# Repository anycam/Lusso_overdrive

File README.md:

# Lusso Overdrive
###### Get a crunch and boost !

This guitar pedal is based on the Klon centaur and the well knwon green friend TS, adding a 2 band EQ for low pass and high pass filtering along with a two modes bypass using two relays and an PIC uC programmed in C++.

Feel free to make your own pedal, here you can find the schematic, pcb and gerber files ready to send into your favorite pcb manufacturer.

## Gallery

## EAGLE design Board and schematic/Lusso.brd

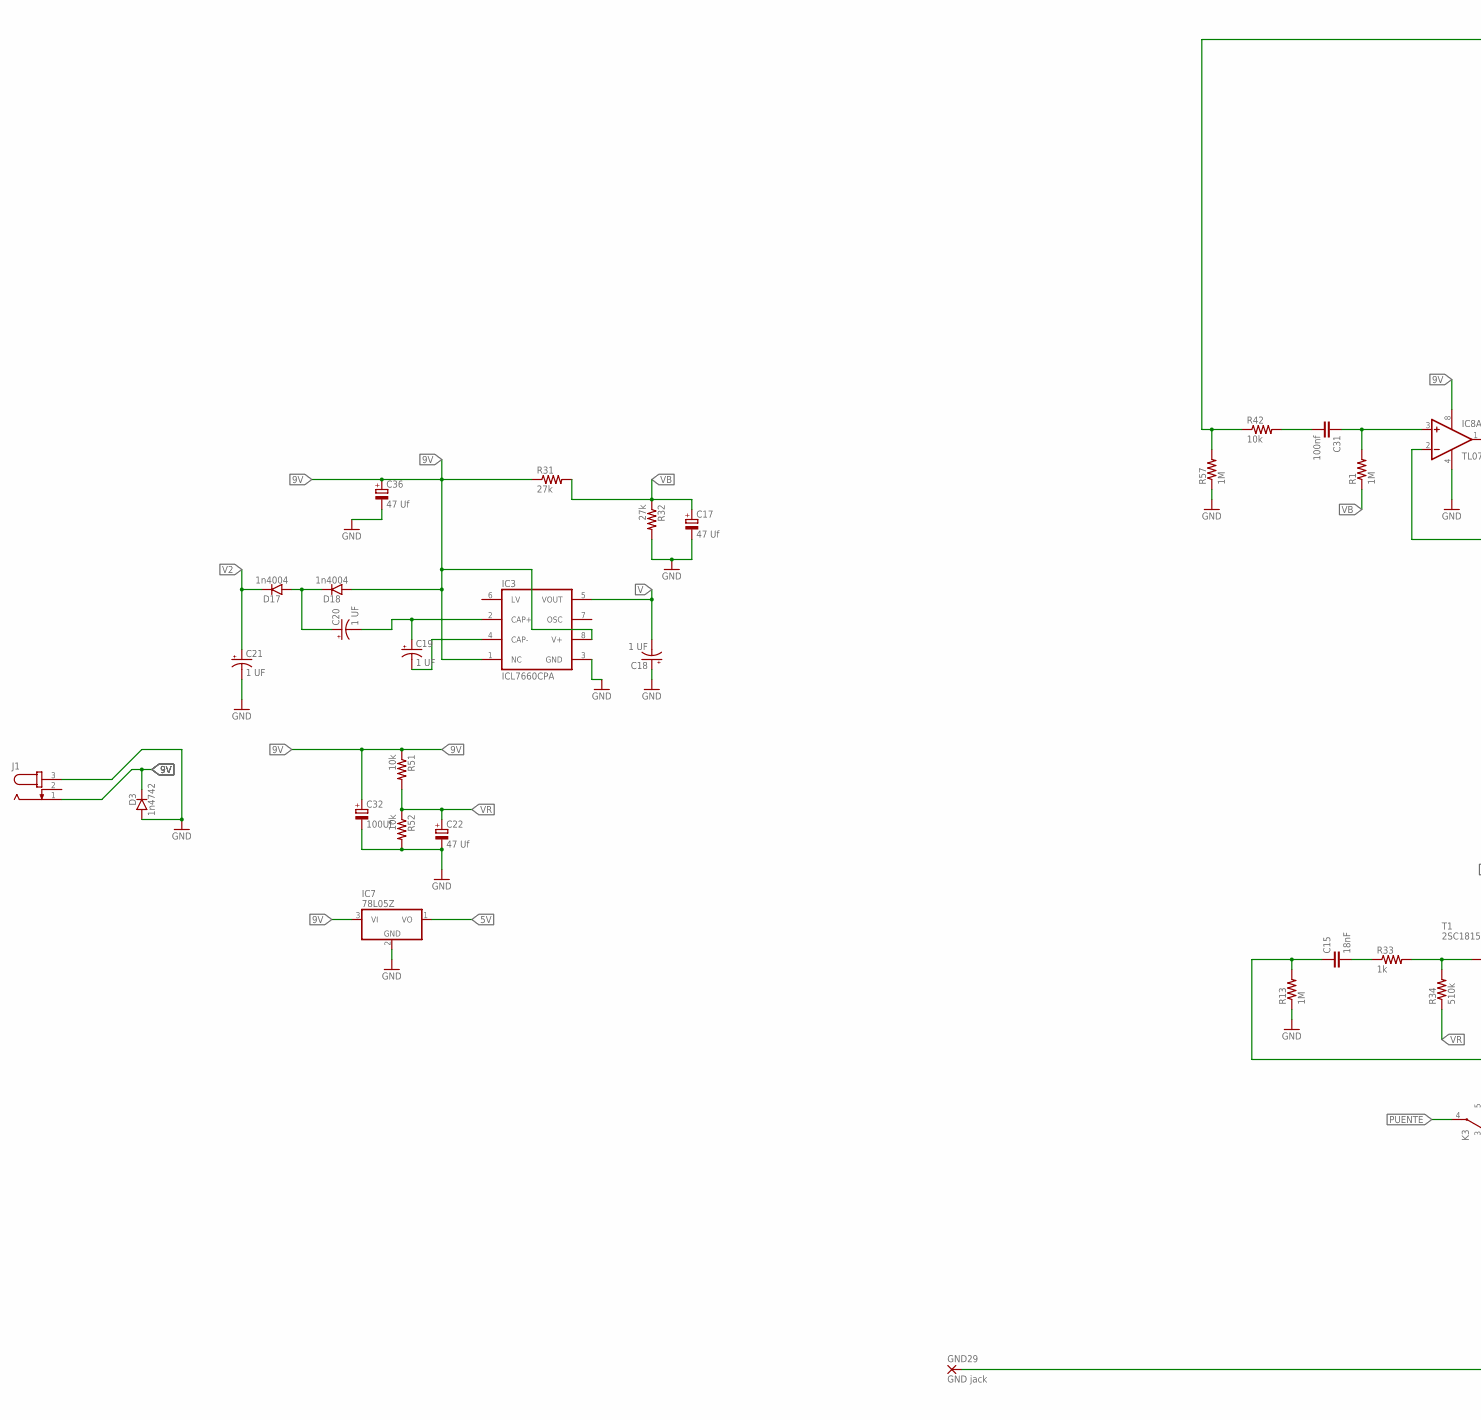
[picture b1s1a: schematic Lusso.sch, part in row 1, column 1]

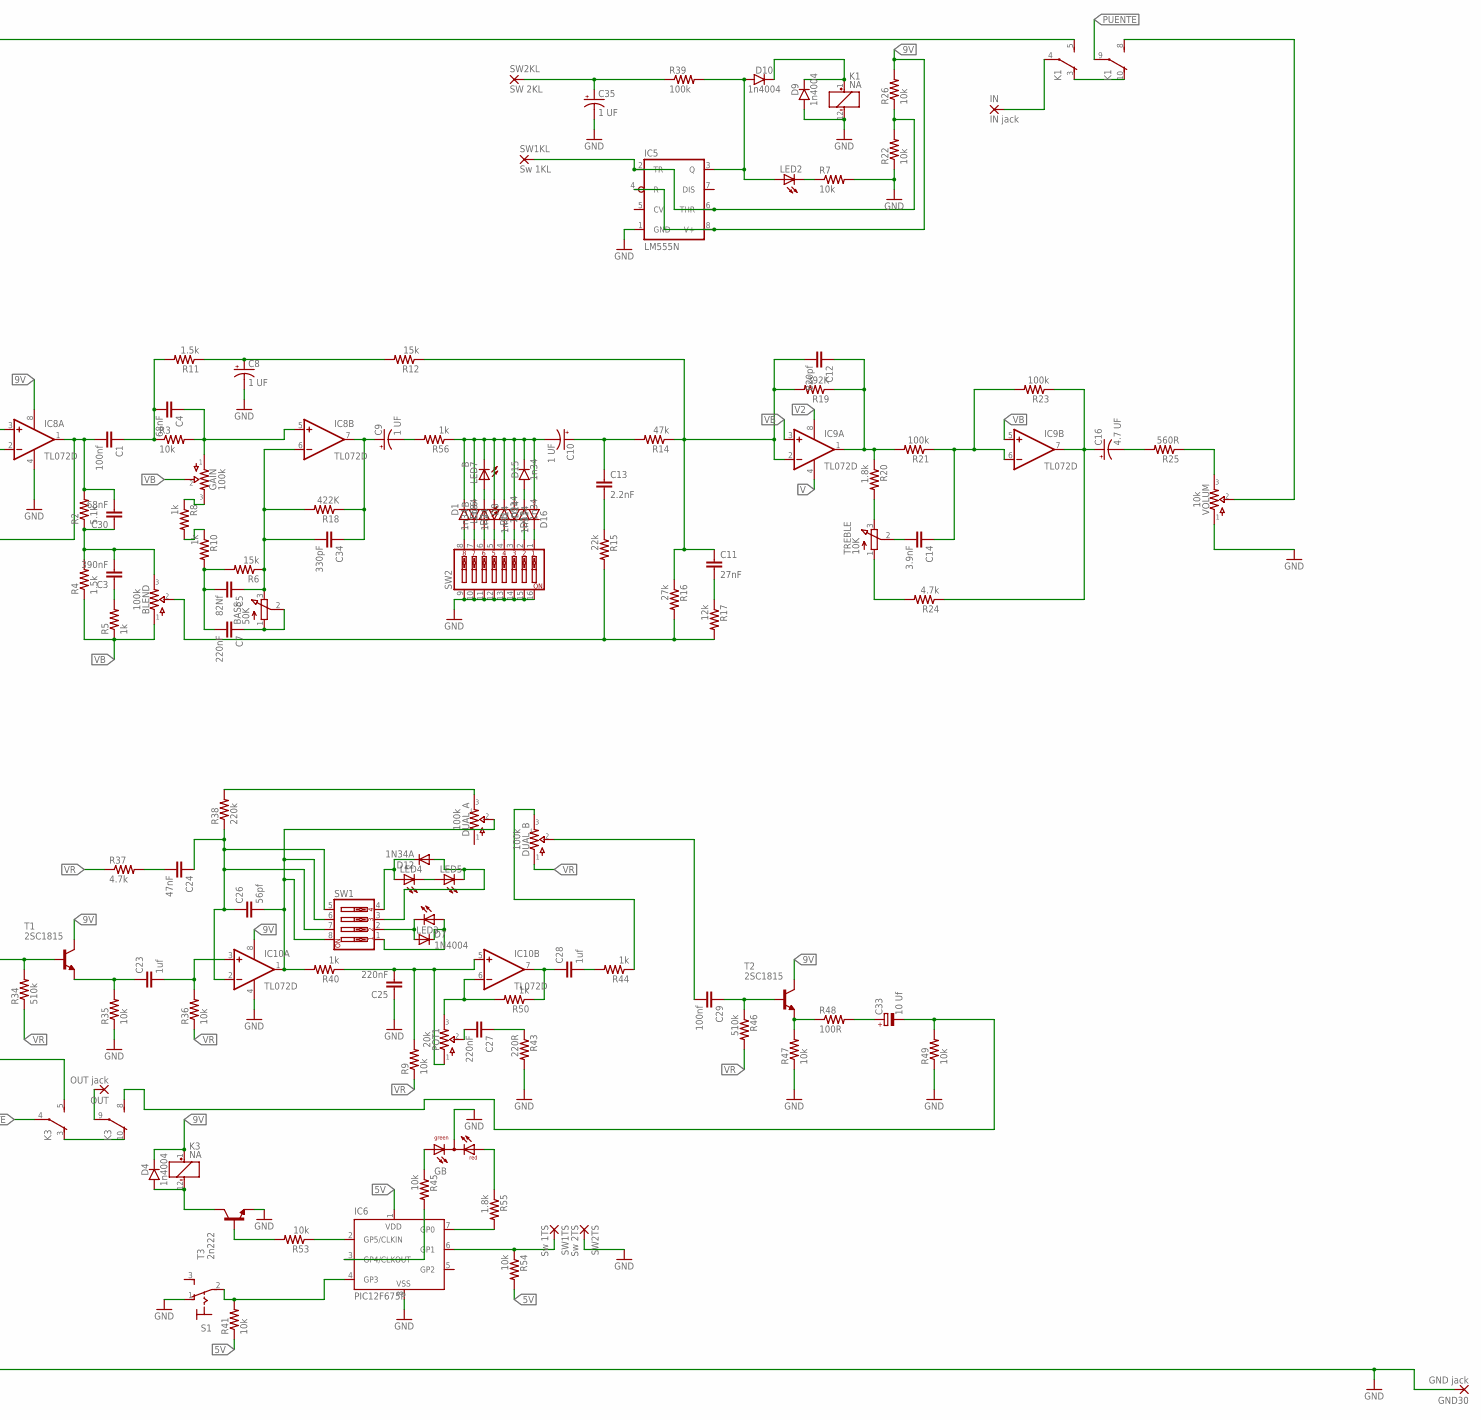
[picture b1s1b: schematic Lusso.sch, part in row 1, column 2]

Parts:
BASS: 50K; EVUF
BLEND: 100k; 16MM_B.MOUNT
C1, C29, C31: 100nf; C0805
C3: 390nF; C2.5-3
C4, C30: 68nF; C0805
C5: 82Nf; C2.5-3
C7, C25, C27: 220nF; C0805
C8, C9, C10, C18, C19, C20, C21, C35: 1 UF; B45181A
C11: 27nF; C2.5-3
C12: 820pf; C0805
C13: 2.2nF; C2.5-3
C14: 3.9nF; C0805
C15: 18nF; C2.5-3
C16: 4.7 UF; B45181A
C17, C22, C36: 47 Uf; PANASONIC_B
C23, C28: 1uf; C1206
C24: 47nF; C0805
C26: 56pf; C0805
C32: 100Uf; PANASONIC_B
C33: 10 Uf; PANASONIC_B
C34: 330pF; C0805
D1, D2, D5, D14, D15: 1n34; DO35-3
D3: 1n4742; DO35-3
D4, D9, D10, D17, D18: 1n4004; DO35-3
D7: 1N4004; DO41-10
D8, D13, D16: 1n914; DO35-3
D12: 1N34A; DO41-10
DUAL: 100k; 16MM_DUALGANG
GAIN: 100k; 16MM_B.MOUNT
GB: DUOLED-RG-C; DUOLED-C-5MM
GND29, GND30: GND jack; 2,15/1,0
IC3: ICL7660CPA; DIL08
IC5: LM555N; DIL08
IC6: PIC12F675P; DIL8
IC7: 78L05Z; TO92
IC8, IC9, IC10: TL072D; SO08
IN: IN jack; 2,15/1,0
J1: JACK-PLUG0; SPC4077
K1, K3: NA
LED2, LED3, LED4, LED5: LED5MM
LED6, LED7: B; LED5MM
OUT: OUT jack; 2,15/1,0
POT1: 20k; TRIM1
R1, R13, R57: 1M; R1206
R2: 5.1k; M0805
R3, R7, R9, R22, R26, R35, R36, R41, R42, R45, R47, R49, R51, R52, R53, R54: 10k; M0805
R4, R11: 1.5k; M0805
R5, R8, R10, R33, R40, R44, R50, R56: 1k; M0805
R6, R12: 15k; M0805
R14: 47k; M0805
R15: 22k; M0805
R16, R31, R32: 27k; M0805
R17: 12k; M0805
R18: 422K; 0204/7
R19: 392K; 0204/7
R20, R55: 1.8k; M0805
R21, R23, R39: 100k; M0805
R24, R37: 4.7k; M0805
R25: 560R; M0805
R34, R46: 510k; M0805
R38: 220k; M0805
R43: 220R; M0805
R48: 100R; M0805
S1: 320-916
SW1: SW_DIP-4; EDG-04
SW1KL: Sw 1KL; 2,15/1,0
SW1TS: Sw 1TS; 2,15/1,0
SW2: SW_DIP-8; EDG-08
SW2KL: SW 2KL; 2,15/1,0
SW2TS: Sw 2TS; 2,15/1,0
T1, T2: 2SC1815; TO92-ECB
T3: 2n222; TO18
TREBLE: 10K; EVUF
VOLUM: 10k; 16MM_B.MOUNT

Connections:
5V: IC6.1 (VDD), IC7.1 (VO), R41.1, R54.2
9V: C32.+, C36.+, D3.C, D4.C, D18.A, IC3.1 (NC), IC3.8 (V+), IC5.4 (R), IC5.8 (V+), IC7.3 (VI), IC8.8 (V+), IC10.8 (V+), J1.1, K3.1 (+), R26.2, R31.1, R51.1, T1.C, T2.C
GND: C8.-, C17.-, C18.+, C21.-, C22.-, C25.1, C32.-, C35.-, C36.-, D3.A, D9.A, GB.C, GND29.1, GND30.1, IC3.3 (GND), IC5.1 (GND), IC6.8 (VSS), IC7.2 (GND), IC8.4 (V-), IC10.4 (V-), J1.3, K1.12 (-), R7.2, R13.1, R22.1, R32.2, R35.1, R43.2, R47.1, R49.1, R52.2, R57.1, S1.1 (O), SW2.9, SW2.10, SW2.11, SW2.12, SW2.13, SW2.14, SW2.15, SW2.16, SW2TS.1, T3.1 (E), VOLUM.1
unnamed: C31.2, R42.2
unnamed: C31.1, IC8.3 (+IN), R1.2
unnamed: C1.2, C30.2, IC8.1 (OUT), IC8.2 (-IN), R2.2
unnamed: BLEND.3, C3.2, C30.1, R2.1, R4.2
unnamed: BASS.1 (A), BASS.2 (S), C7.1
unnamed: C3.1, R5.2
unnamed: C1.1, C4.2, R3.1, R11.2
unnamed: C4.1, GAIN.1, IC8.5 (+IN), R3.2
unnamed: GAIN.3, R8.1
unnamed: C5.2, C7.2, R6.2, R10.2
unnamed: BASS.3 (E), C5.1, C34.2, IC8.6 (-IN), R6.1, R18.2
unnamed: C12.1, IC9.1 (OUT), R19.1, R20.1, R21.2
unnamed: K3.3 (O), K3.10 (O)
unnamed: C8.+, R11.1, R12.2
unnamed: R20.2, TREBLE.3 (E)
unnamed: C9.+, C34.1, IC8.7 (OUT), R18.1
unnamed: C9.-, R56.2
unnamed: C10.-, D1.C, D2.A, D5.A, D8.C, D13.A, D15.C, D16.A, LED7.K (C), R56.1
unnamed: C14.2, TREBLE.2 (S)
unnamed: C10.+, C13.1, R14.2
unnamed: C13.2, R15.1
unnamed: C11.2, R17.1
unnamed: C11.1, C12.2, IC9.2 (-IN), R12.1, R14.1, R16.1, R19.2
unnamed: BLEND.2, R15.2, R16.2, R17.2
unnamed: C14.1, IC9.6 (-IN), R21.1, R23.2
unnamed: C16.+, IC9.7 (OUT), R23.1, R24.1
unnamed: C16.-, R25.2
unnamed: R25.1, VOLUM.3
unnamed: K1.3 (O), K1.10 (O)
unnamed: R8.2, R10.1
unnamed: K1.8 (S), VOLUM.2
unnamed: R24.2, TREBLE.1 (A)
unnamed: DUAL.3, R38.2
unnamed: DUAL.6 (3), R44.1
unnamed: C15.2, R33.1
unnamed: C20.+, D17.A, D18.C
unnamed: C29.2, DUAL.5 (2)
unnamed: C19.+, C20.-, IC3.2 (CAP+)
unnamed: IC5.2 (TR), IC5.6 (THR), R22.2, R26.1, SW1KL.1
unnamed: LED2.K (C), R7.1
unnamed: IC6.4 (GP3), R41.2, S1.2
unnamed: C35.+, R39.1, SW2KL.1
unnamed: D10.A, IC5.3 (Q), LED2.A, R39.2
unnamed: D9.C, D10.C, K1.1 (+)
unnamed: IC6.2 (GP5/CLKIN), R53.1
unnamed: D1.A, SW2.8
unnamed: R33.2, R34.2, T1.B
unnamed: R53.2, T3.2 (B)
unnamed: D4.A, K3.12 (-), T3.3 (C)
unnamed: C23.1, R35.2, T1.E
unnamed: D2.C, SW2.7
unnamed: IC6.3 (GP4/CLKOUT), R45.2
unnamed: C24.1, C26.1, IC10.2 (-IN), R38.1, SW1.5, SW1.7
unnamed: C26.2, DUAL.2, IC10.1 (OUT), R40.2, SW1.6, SW1.8
unnamed: IC6.6 (GP1), R54.1, SW1TS.1
unnamed: C24.2, R37.2
unnamed: IC6.7 (GP0), R55.2
unnamed: C25.2, IC10.5 (+IN), POT1.1, R9.2, R40.1
unnamed: GB.AX (AG), R45.1
unnamed: IC10.6 (-IN), POT1.3, R50.2
unnamed: C27.2, POT1.2
unnamed: C27.1, R43.1
unnamed: C28.1, IC10.7 (OUT), R50.1
unnamed: C28.2, R44.2
unnamed: GB.AR, R55.1
unnamed: D12.C, LED4.A, SW1.4
unnamed: C29.1, R46.1, T2.B
unnamed: R47.2, R48.1, T2.E
unnamed: LED4.K (C), LED5.A
unnamed: C33.+, R48.2
unnamed: C33.-, K3.8 (S), R49.2
unnamed: D12.A, LED5.K (C), SW1.3
unnamed: D7.A, LED3.K (C), SW1.2
unnamed: D7.C, LED3.A, SW1.1
unnamed: LED6.A, SW2.6
unnamed: LED6.K (C), LED7.A
unnamed: C23.2, IC10.3 (+IN), R36.2
unnamed: D5.C, SW2.5
unnamed: D8.A, SW2.4
unnamed: C19.-, IC3.4 (CAP-)
unnamed: D13.C, SW2.3
unnamed: D14.C, D15.A
unnamed: D14.A, SW2.2
unnamed: D16.C, SW2.1
unnamed: C15.1, K3.5 (S), R13.2
unnamed: K1.5 (S), R42.1, R57.2
unnamed: IN.1, K1.4
unnamed: K3.9, OUT.1
PUENTE: K1.9, K3.4
V: C18.-, IC3.5 (VOUT), IC9.4 (V-)
V2: C21.+, D17.C, IC9.8 (V+)
VB: BLEND.1, C17.+, GAIN.2, IC9.3 (+IN), IC9.5 (+IN), R1.1, R4.1, R5.1, R31.2, R32.1
VR: C22.+, DUAL.4 (1), R9.1, R34.1, R36.1, R37.1, R46.2, R51.2, R52.1

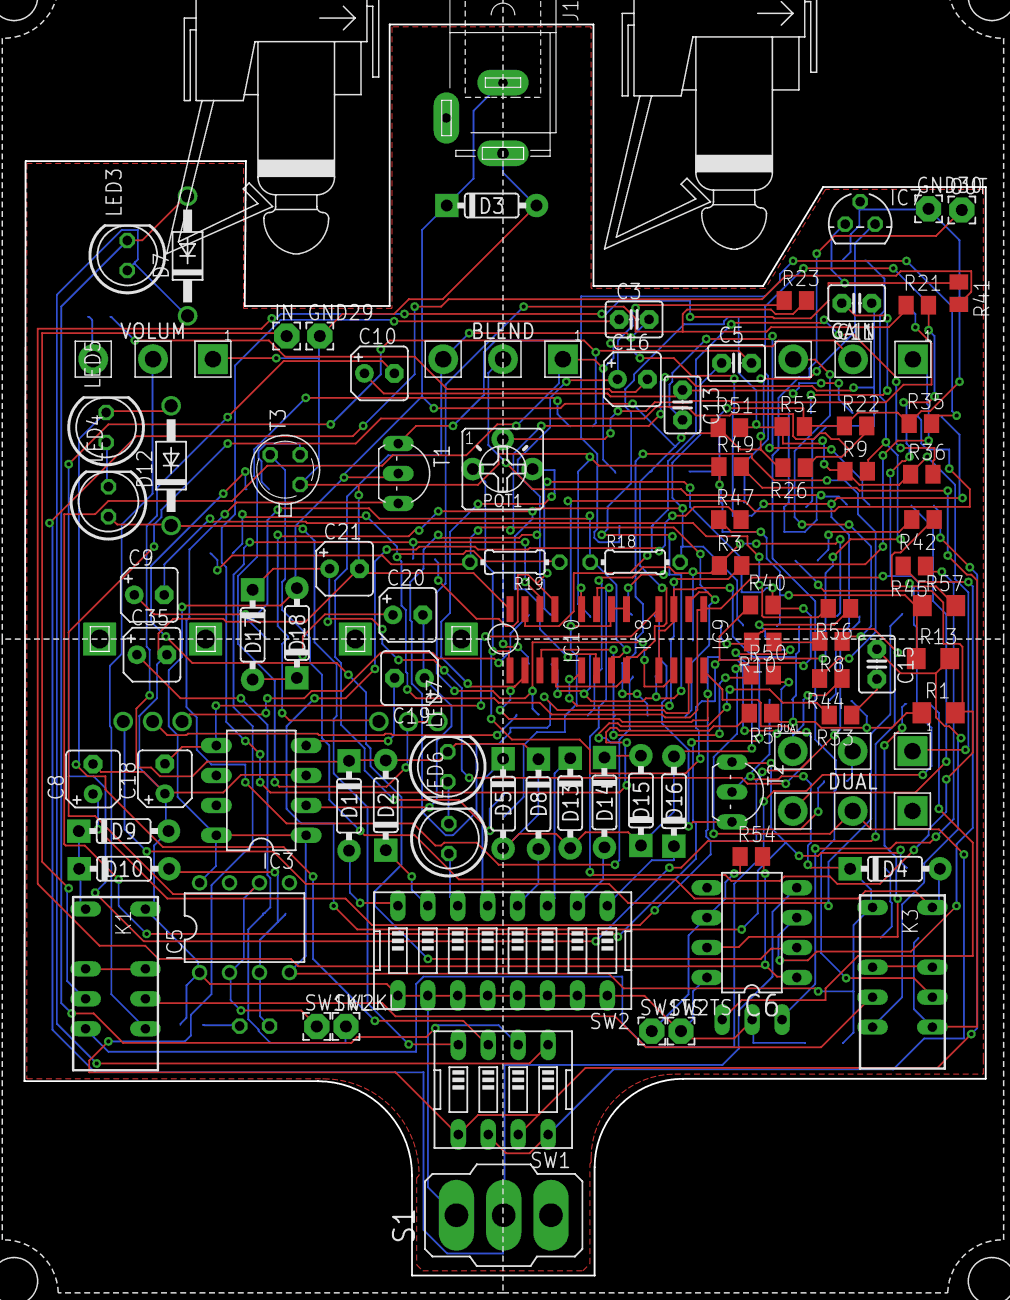
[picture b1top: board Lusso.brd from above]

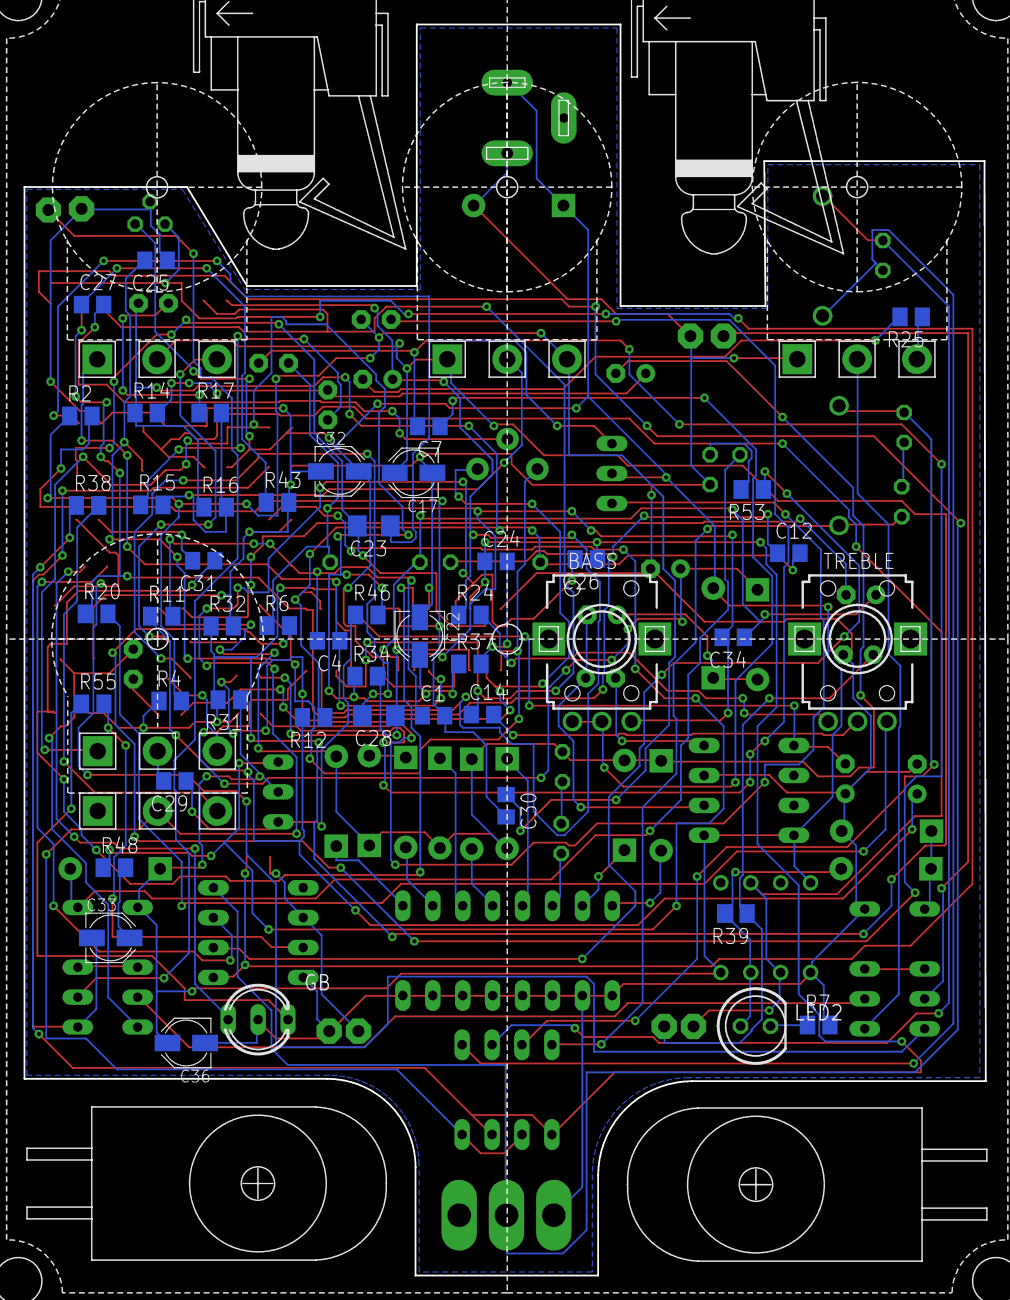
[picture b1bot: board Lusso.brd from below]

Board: 2 copper layers, 81.6 x 106.2 mm, 146 parts (48 on the bottom side), 96 nets.

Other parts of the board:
U$1: 1590BB
U$2, U$3: LUMBURG_SIDE
U$4, U$5: MOMENTARY

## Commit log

2021-02-10 Let's start
2021-02-10 README for lusso
    Quick overview of this project.
2021-02-10 Welcome
    Quick overview of the project
